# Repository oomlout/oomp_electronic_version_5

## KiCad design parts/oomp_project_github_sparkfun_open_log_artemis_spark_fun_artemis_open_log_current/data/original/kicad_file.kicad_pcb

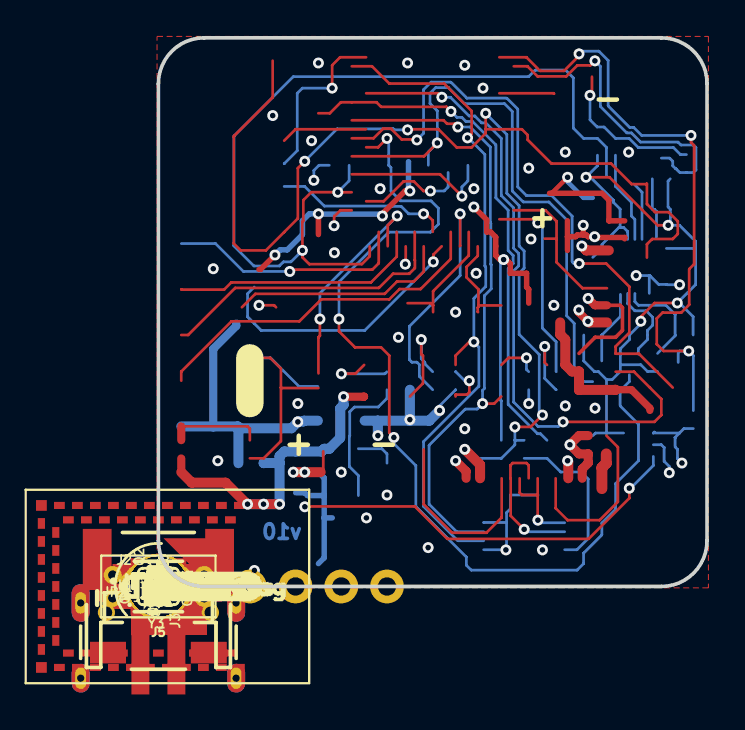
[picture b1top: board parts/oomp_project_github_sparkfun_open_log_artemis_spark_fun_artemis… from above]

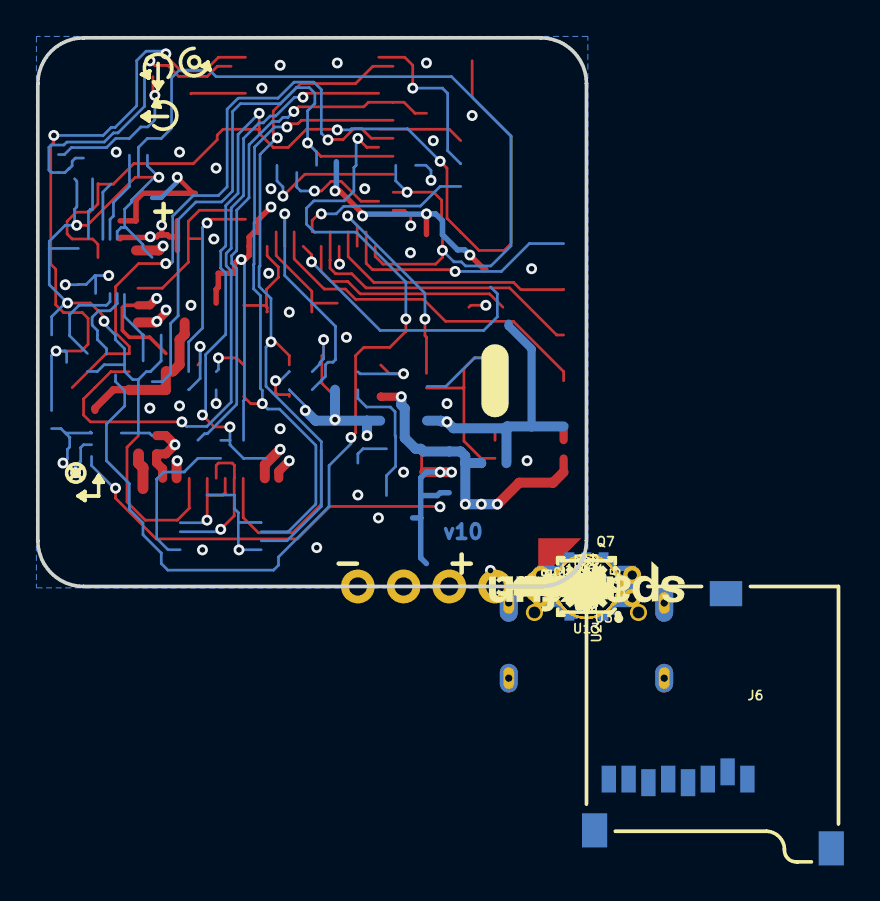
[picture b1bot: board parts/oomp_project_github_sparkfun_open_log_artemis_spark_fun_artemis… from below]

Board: 4 copper layers, 30.5 x 30.5 mm, 140 parts (74 on the bottom side), 61 nets.

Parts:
BT1: ML414H; ML414H_IV01E
C1, C33, C53, C54: 1.0uF; 0402-TIGHT
C2, C7: 2.2uF; 0402-TIGHT
C3, C4: 4.7uF; 0402-TIGHT
C5, C31, C41, C42, C43, C46, C51, C52: 0.1uF; 0402-TIGHT
C29, C30: 15pF; 0402-TIGHT
C32: 10uF; 0402-TIGHT
C40: 10nF; 0402-TIGHT
C44: 1.0nF; 0402-TIGHT
D1, D3: 3A/10V/280mV; SOD-323
D2, D11: Yellow; LED-0603
D6: 1A/23V/620mV; SOD-323
D9: BLUE; LED-0603
D12: GREEN; LED-0603
FD1, FD2, FD3, FD4: FIDUCIAL1X2; FIDUCIAL-1X2
FRAME1: FRAME-LEDGER; CREATIVE_COMMONS
GND0: TEST-POINTTP_15TH_THRU; TP_15TH
H1, H2, H3, H4: STAND-OFF
J1, J3: 1X02_NO_SILK
J2: JST-2-SMD
J4: 1X06_NO_SILK
J5: USB-C-16P_4LAYER-PADS
J6: MICRO-SD; MICRO-SD-SOCKET
J7: 1X01_NO_SILK
J11: QWIIC_RIGHT_ANGLE; JST04_1MM_RA
J14: CORTEX_JTAG; 2X5-PTH-1.27MM
JP2: MEAS; COMBO-JUMPER_2_NC_TRACE
LED1: RED; LED-0603
LOGO1: SFE_LOGO_NAME.1_INCH; SFE_LOGO_NAME_.1
LOGO2: OSHW-LOGOS; OSHW-LOGO-S
LOGO3: SPECIAL_INSTRUCTIONS-ORDERING; ORDERING_INSTRUCTIONS
LOGO4, LOGO5: SFE_LOGO_FLAME.1_INCH; SFE_LOGO_FLAME_.1
Q1, Q3, Q7, Q9, Q10: 20V/0.2A/8MHz/1.2Ω/1Vth; SOT-416FL
Q2: 20V/4.2A/52mΩ/1.4W; SOT23-3
QWIIC_3.3V0: TEST-POINTTP_15TH_THRU; TP_15TH
R1, R4, R40, R41, R44, R45, R46, R47, R48: 2.2k; 0402-TIGHT
R2: 330K; 0402-TIGHT
R3: 220k; 0402-TIGHT
R5, R22, R23, R24, R25: 1k; 0402-TIGHT
R6: 1M; 0402-TIGHT
R7: 2M; 0402-TIGHT
R8: 0; 0402-TIGHT
R26, R27: 5.1k; 0402-TIGHT
R28: 100k; 0402-TIGHT
R29: 220KOHM-0402T-1/16W-1%; 0402-TIGHT
R49: DNP; 0402-TIGHT
S3: RESET; TACTILE_SWITCH_SMD_4.6X2.8MM
SCL0: TEST-POINTTP_15TH_THRU; TP_15TH
SDA0: TEST-POINTTP_15TH_THRU; TP_15TH
TP1: TEST-POINT3; PAD.03X.03
U1: 3.0V Supervisor; SOT23-3
U2: MCP73831; SOT23-5
U3, U4: 3.3V; SOT23-5
U8: ARTEMIS_MODULE; ARTEMIS_FP
U10: CH340E; MSOP10
U13: 9DoF IMU; QFN24-3X3-ICM-20948
U14: 1.8V/100mA; SC70
U$1: QWIIC#LOGO#JPG
U$2: CHG2
U$3: PWR0
U$4: RX4
U$5: STAT5
U$6: VE0
U$7: TX3
U$8, U$12: RST0
U$9: ARTEMIS13
U$10, U$11: PSWC0
U$13: C0
U$14: D0
U$15: 30
U$27: MEAS3
U$28: OPENLOG12
U$32: RST9
U$33: VIN8
U$34, U$35: 3V34
U$36, U$37: 113
U$38, U$39: 322
U$40, U$41: GND5
U$42, U$54: RX1
U$43, U$49: X0
U$44, U$50: Y1
U$45, U$51: Z2
U$46: G5
U$47: A4
U$48: M3
U$55, U$56: TX0
VE0: SMT-JUMPER_2_NO_SILK
Y3: 32.768kHz; CRYSTAL-SMD-3.2X1.5MM

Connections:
3.3V: C2.1, C40.1, C41.1, C54.1, D6.A, J4.5, J14.1, Q2.2, R24.2, R25.2, R45.2, R47.2, R49.2, U1.3, U3.5, U10.7, U10.10, U14.1
5V: C3.1, D1.C, D2.A, J5.VBUS1, J5.VBUS2, JP2.1, JP2.3, U2.4
ARTEMIS_BOOT: C43.2, R29.2, U8.BOOT
ARTEMIS_RX0: D11.C, U8.RXI-0, U10.8
ARTEMIS_SWDCK: J14.4, U8.SWDCK
ARTEMIS_SWDIO: J14.2, U8.SWDIO
ARTEMIS_TX0: D12.C, U8.TXO-0, U10.9
ARTEMIS_~AD11: J4.1, U8.~AD11
ARTEMIS_~AD12/TX1: J4.3, U8.~AD12
ARTEMIS_~AD13/RX1: J4.2, U8.~AD13
ARTEMIS_~AD32: J4.4, U8.~AD32
ARTEMIS_~RESET: C42.2, C44.1, J7.1, J14.10, R28.1, S3.3, S3.4, U8.~RST
ARTEMIS_~RTS: C42.1, C43.1, U10.4
CC3: J5.B5, R26.2
CC4: J5.A5, R27.2
CHG_LED: R5.1, U2.1
D+2: J5.A6, J5.B6, U10.1
D-2: J5.A7, J5.B7, U10.2
DAT1: J6.DAT1, U8.~D26
DAT2: J6.DAT2, U8.~D4
GND: BT1.-, C1.2, C2.2, C3.2, C4.2, C5.2, C7.2, C29.1, C30.1, C31.1, C32.2, C33.2, C40.2, C41.2, C44.2, C46.2, C51.2, C52.2, C53.2, C54.2, D9.C, GND0.P$1, J1.2, J2.1, J3.2, J4.6, J5.GND, J5.GND2, J6.CD1, J6.GND, J6.GND1, J6.GND3, J11.1, J14.3, J14.5, J14.9, LED1.C, R3.1, R4.1, R6.1, R8.1, R26.1, R27.1, R29.1, S3.1, S3.2, U1.1, U2.2, U3.2, U4.2, U8.GND@1, U8.GND@22, U8.GND@38, U8.GND@39, U8.GND@47, U8.GND@59, U10.3, U13.18, U13.20, U14.2
ICM-20948-LV_#_1.8V: C52.1, C53.1, Q1.1, Q3.1, Q7.1, Q9.1, Q10.1, R40.2, R41.2, R44.2, R46.2, R48.2, U13.8, U13.13, U14.5
ICM-20948-LV_INT: Q7.2, R44.1, U13.12
ICM-20948-LV_SCK: Q1.2, R40.1, U13.23
ICM-20948-LV_SDI: Q3.2, R41.1, U13.24
ICM-20948-LV_SDO: Q10.2, R48.1, U13.9
ICM-20948-LV_~CS: Q9.2, R46.1, U13.22
ICM_INT: Q7.3, R45.1, U8.~D37
ICM_PWR: U8.~D27, U14.3
ICM_~CS: Q9.3, R47.1, U8.~D44
MICROSD_PWR: Q2.1, U8.D15
MICROSD_~CS: J6.CS/DAT3, U8.~D23
unnamed: J5.SHLD1, J5.SHLD2, J5.SHLD3, J5.SHLD4, R8.2
unnamed: R4.2, U2.5
unnamed: D2.C, R5.2
unnamed: C29.2, U8.XO, Y3.P$2
unnamed: C30.2, U8.XI, Y3.P$1
unnamed: LED1.A, R22.1
unnamed: D9.A, R23.1
unnamed: D12.A, R25.1
unnamed: D11.A, R24.1
unnamed: C51.1, U13.10
PWR_LED: R22.2, U8.~AD29
QWIIC_3.3V: C5.1, C7.1, J11.2, QWIIC_3.3V0.P$1, U4.5
QWIIC_PWR: R3.2, U4.3, U8.~D18
RTC_BAT+: BT1.+, D3.A, R1.1, TP1.P$1
SCK: J6.SCLK, Q1.3, U8.~D5
SCL: J11.4, SCL0.P$1, U8.D8
SDA: J11.3, SDA0.P$1, U8.D9
SDI: J6.DO/DAT0, Q10.3, R49.1, U8.~D6, U8.~D22
SDO: J6.DI/CMD, Q3.3, U8.D7
SD_PWR: C46.1, J6.VCC, Q2.3
STATLED: R23.2, U8.~D19
SWO: J14.6, U8.~AD33/SWO
VCC_1: C31.2, C32.1, C33.1, D3.C, D6.C, R1.2, R28.2, U8.VDD@36, U8.VDD@37
VIN: C1.1, JP2.2, JP2.4, R2.2, R7.2, U3.1, U4.1
VIN/3: R6.2, R7.1, U8.AD34
VREG_EN: J3.1, R2.1, U3.3, VE0.2
VREG_EN1: U8.~D25, VE0.1
V_BATT: C4.1, D1.A, J1.1, J2.2, U2.3
~POWER_LOSS: U1.2, U8.D3

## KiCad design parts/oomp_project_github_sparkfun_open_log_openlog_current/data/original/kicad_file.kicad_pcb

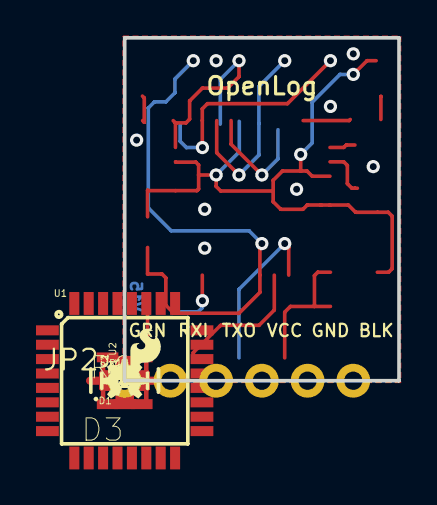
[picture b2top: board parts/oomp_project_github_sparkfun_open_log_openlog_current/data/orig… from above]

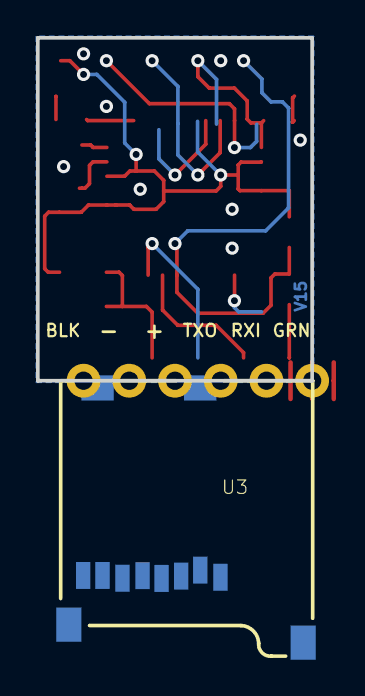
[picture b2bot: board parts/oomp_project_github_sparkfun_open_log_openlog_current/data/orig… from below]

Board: 2 copper layers, 15.2 x 19.1 mm, 26 parts (3 on the bottom side), 17 nets.

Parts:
C1: 10uF; 0603-POL
C2, C3, C4: 0.1uF; 0603-CAP
D1: BLUE; LED-0603
D3: GREEN; LED-0603
FID1, FID2, FID3, FID4: FIDUCIALUFIDUCIAL; MICRO-FIDUCIAL
FRAME1: FRAME-LETTER; CREATIVE_COMMONS
JP2: 1X06_NO_SILK
LOGO1: SFE_LOGO_FLAME.1_INCH; SFE_LOGO_FLAME_.1
LOGO2: OSHW-LOGOMINI; OSHW-LOGO-MINI
Q1: 16MHZ; RESONATOR-SMD
R1: 1K; 0603-RES
R2: 10K; 0603-RES
R6: 330; 0603-RES
TP1, TP2, TP3, TP4, TP5: TEST-POINT3; PAD.03X.03
U1: ATMEGA328P_TQFP; TQFP32-08
U2: 3.3V MIC5205; SOT23-5
U3: microSD Socket; MICROSD_1_1

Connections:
3.3V: C1.A, C3.2, C4.1, R2.2, TP1.P$1, U1.4, U1.6, U1.18, U1.20, U2.5, U3.4
CD: U1.25, U3.CD1
CS: U1.14, U3.2
DTR: C2.2, JP2.6
GND: C1.K, C3.1, C4.2, D1.C, D3.C, JP2.1, JP2.2, Q1.2, U1.3, U1.5, U1.21, U2.2, U3.6, U3.GND1, U3.GND3
MISO: TP2.P$1, U1.16, U3.7
MOSI: TP3.P$1, U1.15, U3.3
unnamed: Q1.1, U1.8
unnamed: Q1.3, U1.7
unnamed: D1.A, R1.2
unnamed: R1.1, U1.9
unnamed: D3.A, R6.2
RAW: JP2.3, U2.1, U2.3
RST: C2.1, R2.1, TP5.P$1, U1.29
RXI: JP2.5, U1.30
SCK: R6.1, TP4.P$1, U1.17, U3.5
TXO: JP2.4, U1.31

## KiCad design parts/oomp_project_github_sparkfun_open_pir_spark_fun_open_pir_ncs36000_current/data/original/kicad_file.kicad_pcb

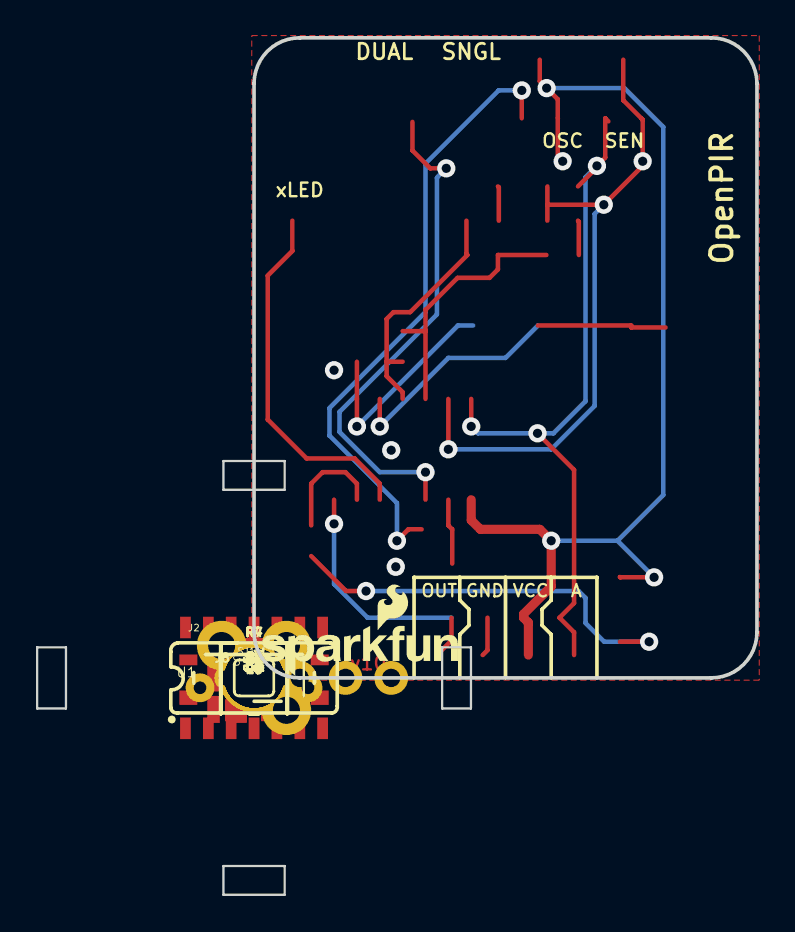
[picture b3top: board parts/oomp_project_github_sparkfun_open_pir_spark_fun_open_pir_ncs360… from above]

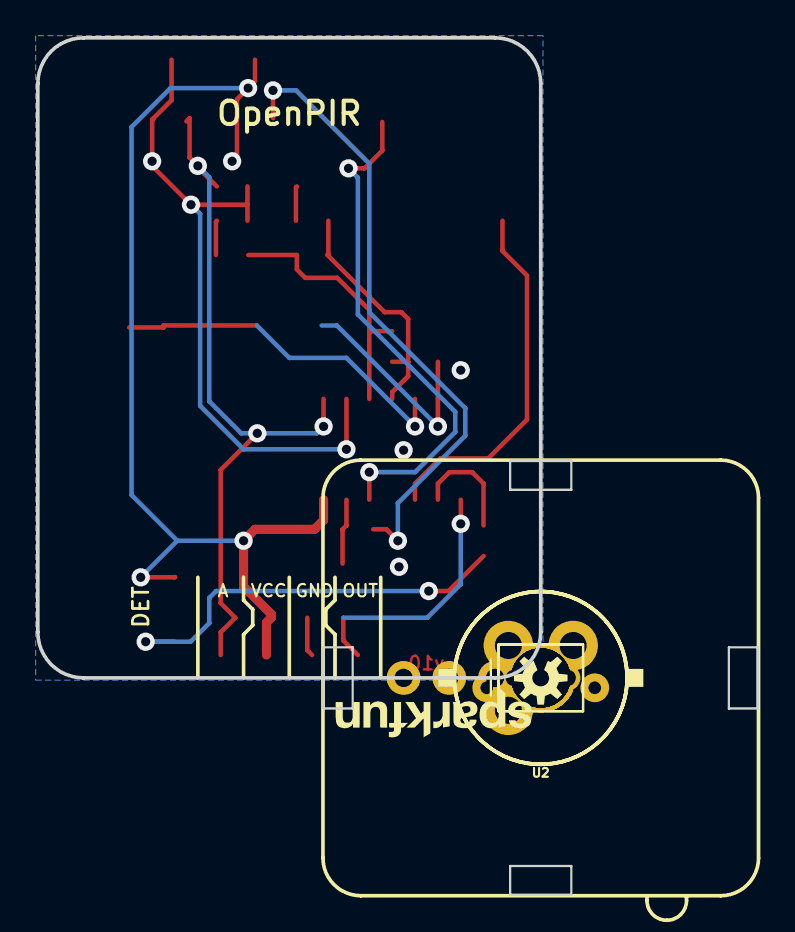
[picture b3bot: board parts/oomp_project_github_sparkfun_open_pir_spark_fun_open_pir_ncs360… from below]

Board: 2 copper layers, 27.9 x 35.6 mm, 35 parts (6 on the bottom side), 17 nets.

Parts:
C1, C3: 22uF; 0805
C2, C4: 10nF; 0603
C5, C6, C7: 0.1uF; 0603
D1: Green; LED-1206-BOTTOM
FD1, FD2: FIDUCIALUFIDUCIAL; MICRO-FIDUCIAL
FRAME1: FRAME-LETTER; CREATIVE_COMMONS
H1, H2, H3, H4: STAND-OFF
J2: JST-4-PTH-VERT-NS
J8: 1X04_NO_SILK_ALL_ROUND
LOGO1: SFE_LOGO_NAME_FLAME.1_INCH; SFE_LOGO_NAME_FLAME_.1
LOGO3: SFE_LOGO_NAME.1_INCH; SFE_LOGO_NAME_.1
LOGO4: OSHW-LOGOS; OSHW-LOGO-S
R1, R3: 10k; 0603
R2: 560k; 0603
R4, R7: 1M; TRIMPOT-TC33X
R5: 43k; 0603
R6: 51k; 0603
R8: 1k; 0603
S1: SWITCH-SPST-SMD-A
SJ1: LED-EN; SJ_2S
TP1, TP2: PAD.03X.05
U1: NCS36000; SO14
U2: PIR
U$1: CWM 0.5 GI V1; LENS-CWM-0.5-GI-V1

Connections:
A_OUT: C4.2, J2.1, J8.1, R4.1, U1.1
GND: C5.2, C6.2, C7.2, J2.3, J8.3, R1.1, R5.1, S1.3, SJ1.2, U1.7, U2.G
LED: R8.1, U1.9
MODE: S1.2, U1.12
unnamed: C5.1, R5.2, U1.5, U2.S
unnamed: C6.1, U1.6, U2.D
unnamed: C1.2, R1.2
unnamed: C3.2, R3.2
unnamed: C1.1, C2.2, R2.1, U1.4
unnamed: C2.1, C3.1, R2.2, U1.3
unnamed: C4.1, R3.1, R4.2, R4.3, TP1.P$1, U1.2
unnamed: C7.1, R6.1, U1.13
unnamed: D1.C, R8.2
unnamed: R6.2, R7.1
OUT: J2.4, J8.4, U1.8
VCC: D1.A, J2.2, J8.2, R7.2, R7.3, TP2.P$1, U1.14
~LED_EN: SJ1.1, U1.10

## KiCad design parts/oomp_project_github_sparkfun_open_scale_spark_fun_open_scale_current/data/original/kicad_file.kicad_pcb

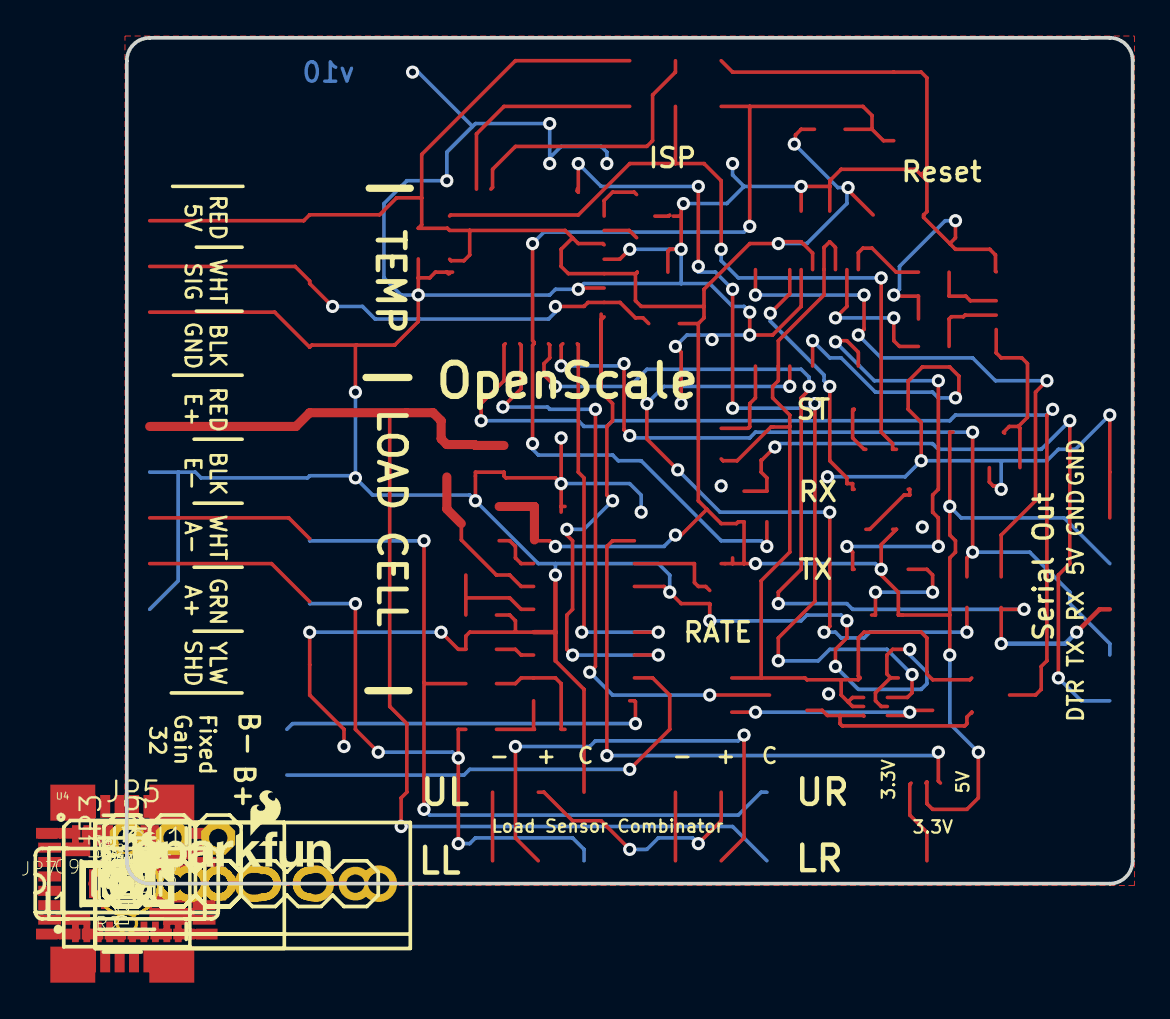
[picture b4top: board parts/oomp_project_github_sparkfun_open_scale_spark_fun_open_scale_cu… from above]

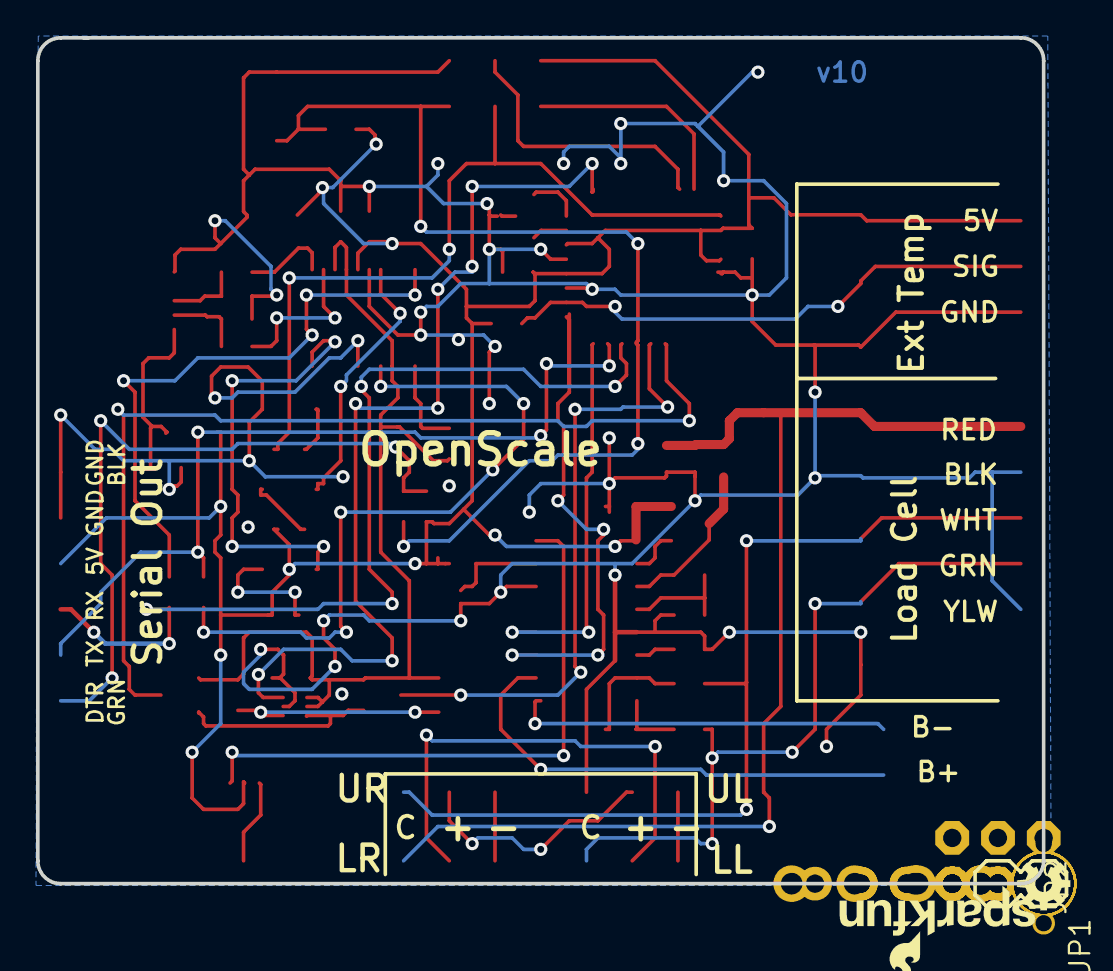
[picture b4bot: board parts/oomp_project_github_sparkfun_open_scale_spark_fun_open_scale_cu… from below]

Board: 2 copper layers, 55.9 x 47.0 mm, 75 parts (4 on the bottom side), 51 nets.

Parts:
C1, C3, C6, C7, C8, C10, C11, C14, C16: 0.1uF; 0603-CAP
C2, C5: 47pF; 0603-CAP
C4, C12, C13: 1.0uF; 0603-CAP
C9: 10uF; EIA3216
D1: Yellow; LED-1206
D2: GREEN; LED-1206
D3: BLUE; LED-1206
F1: PTCSMD; PTC-1206
FID1, FID2: FIDUCIALUFIDUCIAL; MICRO-FIDUCIAL
FRAME1: FRAME-LEDGER; CREATIVE_COMMONS
J1: 3.3V; 1X01
J2: UL; 1X03
J3: UR; 1X03
J4: LL; 1X03
J5: LR; 1X03
JP1: Temp; 1X03_NO_SILK
JP2: Fixed Gain 32; 1X02
JP3: Load; 1X05_NO_SILK
JP4: Screw; SCREWTERMINAL-3.5MM-3_LOCK.007S
JP5: AVR_PRG; 2X3
JP6: JUMPER-PAD-3-2OF3_NC_BY_PASTE; PAD-JUMPER-3-2OF3_NC_BY_PASTE_YES_SILK_FULL_BOX
JP7: USBSMD; USB-MINIB
JP9: FTDI_BASIC
JP11: Screw Terminals; SCREWTERMINAL-3.5MM-5
L1: 3.3uH; 0805
LOGO1, LOGO4: SFE_LOGO_NAME_FLAME.1_INCH; SFE_LOGO_NAME_FLAME_.1
LOGO2, LOGO5: OSHW-LOGOS; OSHW-LOGO-S
LOGO3: SFE_LOGO_FLAME.1_INCH; SFE_LOGO_FLAME_.1
Q1, Q2: 200mA/50V; SOT23-3
Q3: MMBT4403; SOT23-3
Q4: MOSFET-NCHANNEL2N7002PW; SOT323
R1, R6: 27; 0603
R2, R7, R10, R18: 10K; 0603-RES
R3, R4: 100; 0603-RES
R5, R11, R12, R13, R15: 1K; 0603-RES
R8, R9, R14: 4.7K; 0603-RES
R16: 20k; 0603-RES
R17: 8.2K; 0603-RES
S2: Reset; TACTILE-SWITCH-SMD
SJ2: JUMPER-PAD-2-NC_BY_PASTE; PAD-JUMPER-2-NC_BY_PASTE_YES_SILK
STANDOFF1, STANDOFF2, STANDOFF3, STANDOFF4: STAND-OFF
U1: HX711; SO16
U3: TMP102; SOT563
U4: ATMEGA328P_TQFP; TQFP32-08
U6: FT231XS; SSOP20_L
Y2: 16MHZ; RESONATOR-SMD

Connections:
2: J4.2, J5.2
3.3V: C3.1, C10.1, Q1.1, Q2.1, Q4.1, R8.2, R9.2, R10.2, U3.4, U3.5, U6.3, U6.13, U6.14
5V: C4.1, C6.1, C7.1, C9.A, C13.1, F1.2, JP1.1, JP4.1, JP5.2, JP6.2, JP9.VCC, Q3.2, R2.2, R7.2, R13.2, R14.2, R15.2, R18.2, U1.1, U4.4, U4.6, U4.18, U4.20, U6.15
A+: J4.3, JP3.2, JP11.4, R4.1
A-: J3.3, JP3.3, JP11.3, R3.1
ALERT: U3.3, U4.9
AVDD: C12.2, C16.1, J5.3, JP3.5, JP11.1, L1.1
B+: JP2.1, U1.10
B-: JP2.2, U1.9
D11: JP5.4, U4.15
D12: JP5.1, U4.16
D13: JP5.3, R5.2, U4.17
DTR: C1.1, JP9.DTR, Q4.3, R18.1
GND: C2.2, C3.2, C4.2, C5.2, C6.2, C7.2, C9.C, C10.2, C11.1, C12.1, C13.2, C14.2, C16.2, D3.C, J2.3, JP1.3, JP3.1, JP3.4, JP4.3, JP5.6, JP7.GND, JP9.CTS, JP9.GND, JP11.2, JP11.5, R17.1, S2.1, SJ2.1, U1.5, U1.14, U3.2, U4.3, U4.5, U4.21, U6.6, U6.16, Y2.2
LC_DOUT: U1.12, U4.32
LC_SCK: U1.11, U4.1
LV_SCL: Q2.2, R8.1, U3.1
LV_SDA: Q1.2, R9.1, U3.6
unnamed: U4.7, Y2.1
unnamed: D3.A, R5.1
unnamed: U4.8, Y2.3
unnamed: C5.1, JP7.D-, R6.1
unnamed: D1.A, R13.1
unnamed: D2.A, R15.1
unnamed: C2.1, JP7.D+, R1.1
unnamed: R6.2, U6.12
unnamed: R7.1, SJ2.2, U1.15
unnamed: C8.1, R3.2, U1.7
unnamed: C8.2, R4.2, U1.8
unnamed: C14.1, F1.1, JP7.VBUS
unnamed: R1.2, U6.11
unnamed: R12.2, U6.4
unnamed: JP6.3, U1.16
unnamed: R11.2, U6.20
unnamed: Q3.1, U1.2
unnamed: R16.1, R17.2, U1.4
unnamed: J1.1, JP6.1
unnamed: J2.2, J3.2
unnamed: C11.2, U1.6
unnamed: J2.1, J4.1
unnamed: J3.1, J5.1
unnamed: Q4.2, R10.1, U6.1
RIPUP@: L1.2, Q3.3, R16.2, U1.3
RST: C1.2, JP5.5, R2.1, S2.3, U4.29
RXD: JP9.TXO, R11.1, U4.30
RXLED: D1.C, U6.17
SCL: Q2.3, U4.28
SDA: Q1.3, U4.27
TEMP_DAT: JP1.2, JP4.2, R14.1, U4.2
TXD: JP9.RXI, R12.1, U4.31
TXLED: D2.C, U6.10

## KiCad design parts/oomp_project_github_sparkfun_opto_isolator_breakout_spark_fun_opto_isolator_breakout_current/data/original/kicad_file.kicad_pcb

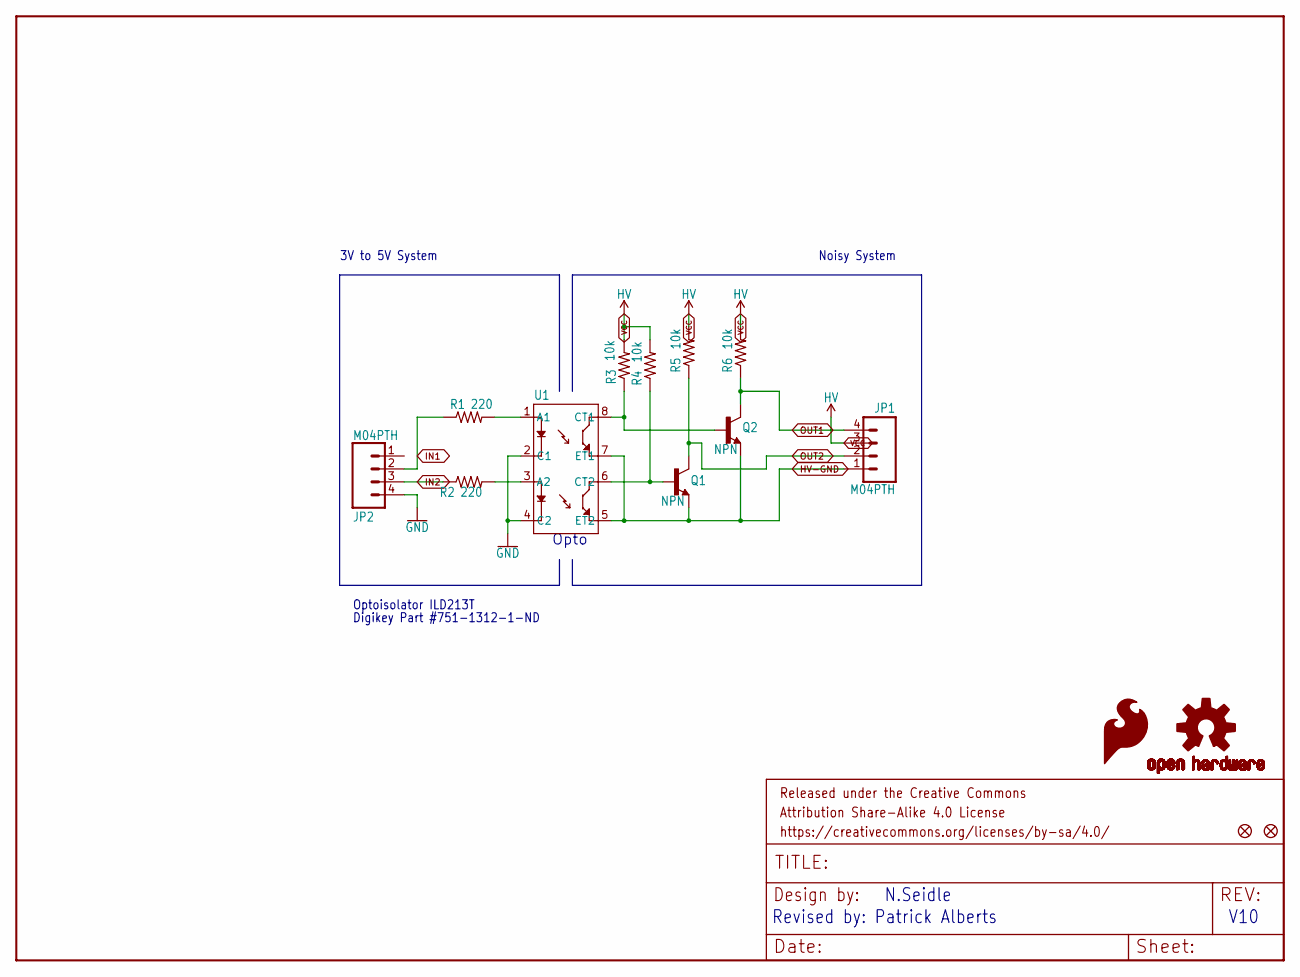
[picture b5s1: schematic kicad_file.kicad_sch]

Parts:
FRAME1: FRAME-LETTER; CREATIVE_COMMONS
JP1, JP2: M04PTH; 1X04
LOGO1: OSHW-LOGOS; OSHW-LOGO-S
LOGO2: SFE_LOGO_FLAME.1_INCH; SFE_LOGO_FLAME_.1
Q1, Q2: NPN; SOT23-3
R1, R2: 220; 0603
R3, R4, R5, R6: 10k; 0603
U1: ILD213T-IDL213T; SO08
U$2, U$3: FIDUCIALUFIDUCIAL; MICRO-FIDUCIAL

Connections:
GND: JP2.4, U1.2 (C1), U1.4 (C2)
HV-GND: JP1.1, Q1.2 (E), Q2.2 (E), U1.5 (ET2), U1.7 (ET1)
IN1: JP2.2, R1.1
IN2: JP2.3, R2.1
unnamed: R1.2, U1.1 (A1)
unnamed: R2.2, U1.3 (A2)
OUT1: JP1.4, Q2.3 (C), R6.1
OUT1N: Q2.1 (B), R3.1, U1.8 (CT1)
OUT2: JP1.2, Q1.3 (C), R5.1
OUT2N: Q1.1 (B), R4.1, U1.6 (CT2)
VCC: JP1.3, R3.2, R4.2, R5.2, R6.2

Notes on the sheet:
Optoisolator ILD213T
Opto
Noisy System
V10
Digikey Part #751-1312-1-ND
N.Seidle
3V to 5V System
Revised by: Patrick Alberts

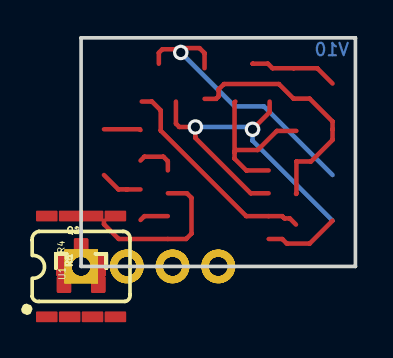
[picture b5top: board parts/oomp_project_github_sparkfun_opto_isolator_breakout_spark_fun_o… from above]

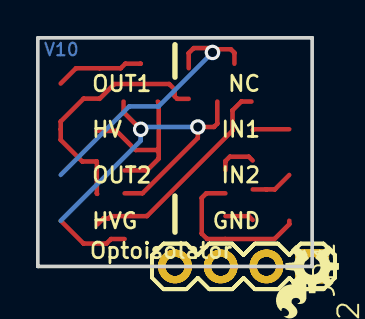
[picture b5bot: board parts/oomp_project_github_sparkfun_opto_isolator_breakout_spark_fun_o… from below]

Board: 2 copper layers, 15.2 x 12.7 mm, 16 parts (4 on the bottom side), 11 nets.

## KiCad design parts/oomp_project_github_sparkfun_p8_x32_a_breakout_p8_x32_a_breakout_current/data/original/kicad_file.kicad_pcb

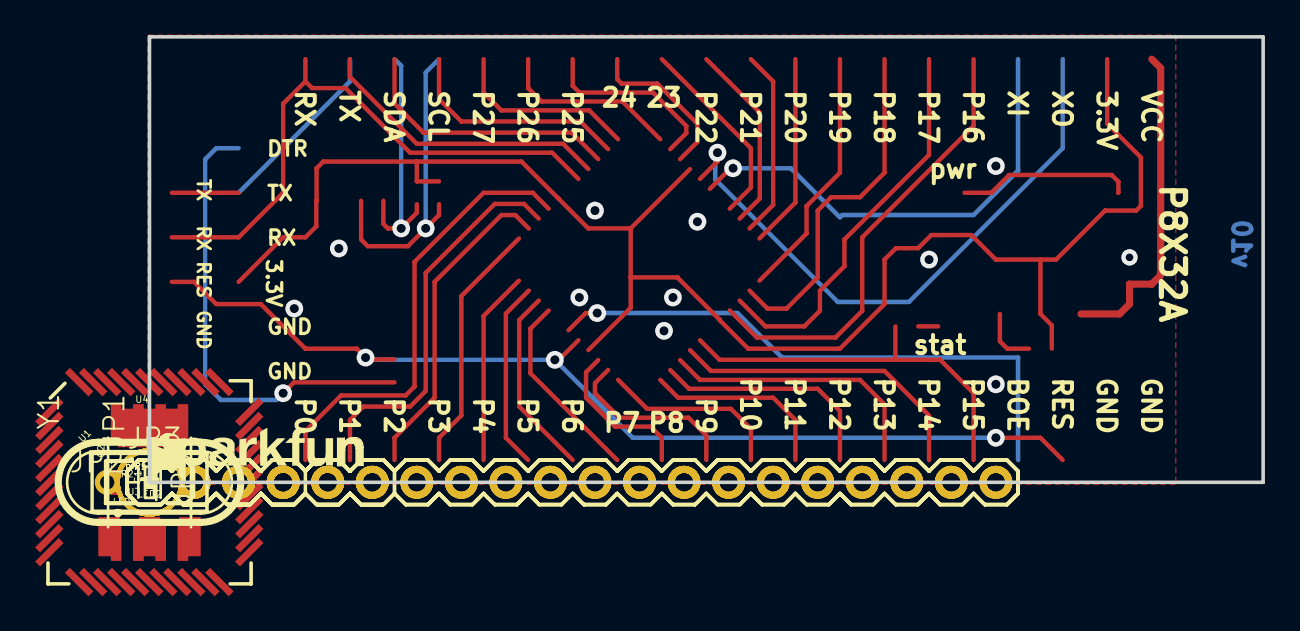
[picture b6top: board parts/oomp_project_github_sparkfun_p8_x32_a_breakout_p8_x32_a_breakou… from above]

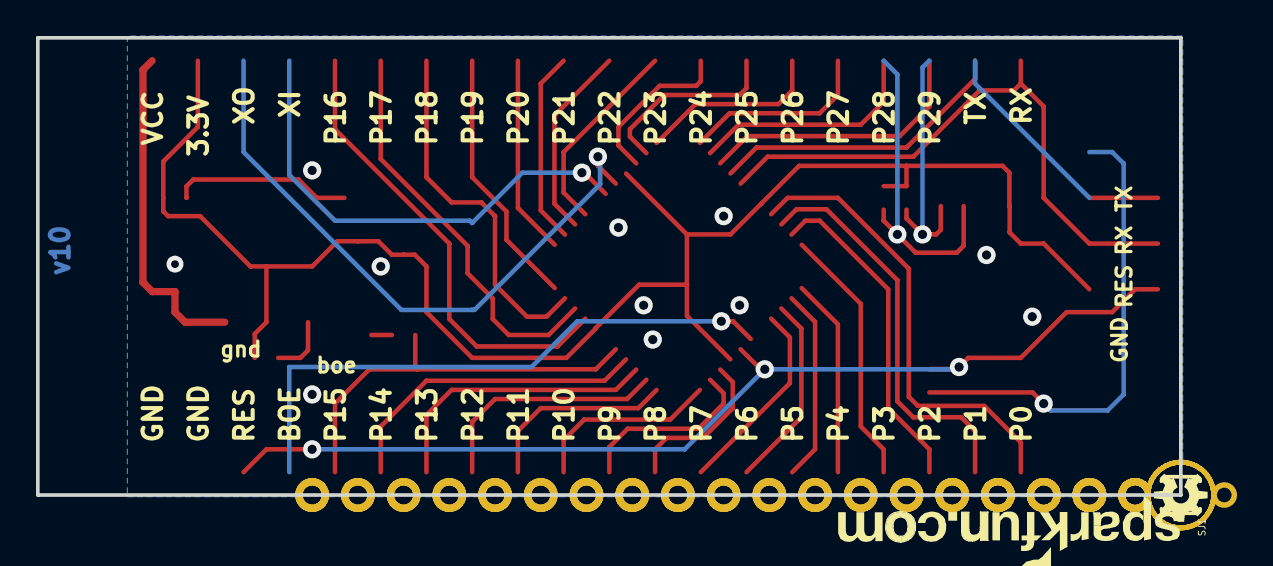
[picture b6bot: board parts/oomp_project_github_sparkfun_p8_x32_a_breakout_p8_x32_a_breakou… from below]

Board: 2 copper layers, 63.5 x 25.4 mm, 34 parts (3 on the bottom side), 43 nets.

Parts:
C1, C4: 0.1uF; 0402-CAP
C2, C3: 10uF; EIA3216
FRAME1: FRAME-LETTER; CREATIVE_COMMONS
JP1: PropPlug; 1X04
JP2, JP3: M20; 1X20
JP4, JP15: FIDUCIALUFIDUCIAL; MICRO-FIDUCIAL
JP5: LOGO-SFENEW; SFE-NEW-WEBLOGO
JP6, JP7, JP8: LOGO-SFESK; SFE-LOGO-FLAME
JP9: FTDI_BASICPTH; FTDI_BASIC
JP10, JP11, JP12, JP13: STAND-OFF
JP14: LOGO-SFENW2; SFE-NEW-WEB
LED1: red; LED-0603
LED2: yellow; LED-0603
R1, R2: 330; 0402-RES
R3, R6: 10k; 0402-RES
R4: 240; 0402-RES
R5: 390; 0402-RES
SJ1: SOLDERJUMPERTRACE; SJ_2S-TRACE
U1: P8X32A-Q44
U3: EEPROM-I2CEIAJ; SO08-EIAJ
U4: V_REG_317SMD; SOT223
U$1: OSHW-LOGOS; OSHW-LOGO-S
Y1: HC49U-V

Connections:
3.3V: C1.1, C2.A, JP3.19, JP9.VCC, R1.2, R3.2, R4.2, R6.2, U1.8, U1.18, U1.30, U1.40, U3.8, U4.2
BOE: JP2.4, SJ1.2, U1.6
GND: C1.2, C2.C, C3.C, JP1.1, JP2.1, JP2.2, JP9.CTS, JP9.GND, LED1.C, LED2.C, R5.1, SJ1.1, U1.5, U1.17, U1.27, U1.39, U3.1, U3.2, U3.3, U3.4, U3.7
unnamed: LED1.A, R1.1
unnamed: LED2.A, R2.1
unnamed: R4.1, R5.2, U4.1
unnamed: C4.1, JP9.DTR
P0: JP2.20, U1.41
P1: JP2.19, U1.42
P2: JP2.18, U1.43
P3: JP2.17, U1.44
P4: JP2.16, U1.1
P5: JP2.15, U1.2
P6: JP2.14, U1.3
P7: JP2.13, U1.4
P8: JP2.12, U1.9
P9: JP2.11, U1.10
P10: JP2.10, U1.11
P11: JP2.9, U1.12
P12: JP2.8, U1.13
P13: JP2.7, U1.14
P14: JP2.6, U1.15
P15: JP2.5, R2.2, U1.16
P16: JP3.16, U1.19
P17: JP3.15, U1.20
P18: JP3.14, U1.21
P19: JP3.13, U1.22
P20: JP3.12, U1.23
P21: JP3.11, U1.24
P22: JP3.10, U1.25
P23: JP3.9, U1.26
P24: JP3.8, U1.31
P25: JP3.7, U1.32
P26: JP3.6, U1.33
P27: JP3.5, U1.34
RES: C4.2, JP1.2, JP2.3, U1.7
RX: JP1.3, JP3.1, JP9.TXO, U1.38
SCL: JP3.4, R6.1, U1.35, U3.6
SDA: JP3.3, R3.1, U1.36, U3.5
TX: JP1.4, JP3.2, JP9.RXI, U1.37
VCC: C3.A, JP3.20, U4.3
XI: JP3.17, U1.28, Y1.2
XO: JP3.18, U1.29, Y1.1

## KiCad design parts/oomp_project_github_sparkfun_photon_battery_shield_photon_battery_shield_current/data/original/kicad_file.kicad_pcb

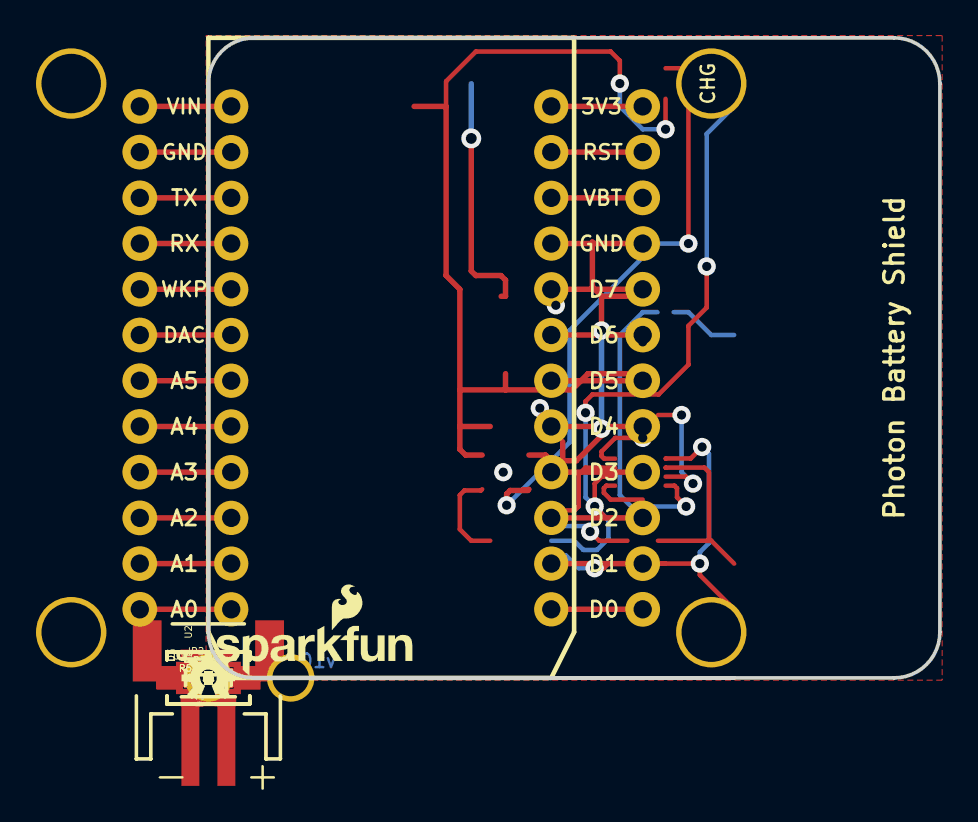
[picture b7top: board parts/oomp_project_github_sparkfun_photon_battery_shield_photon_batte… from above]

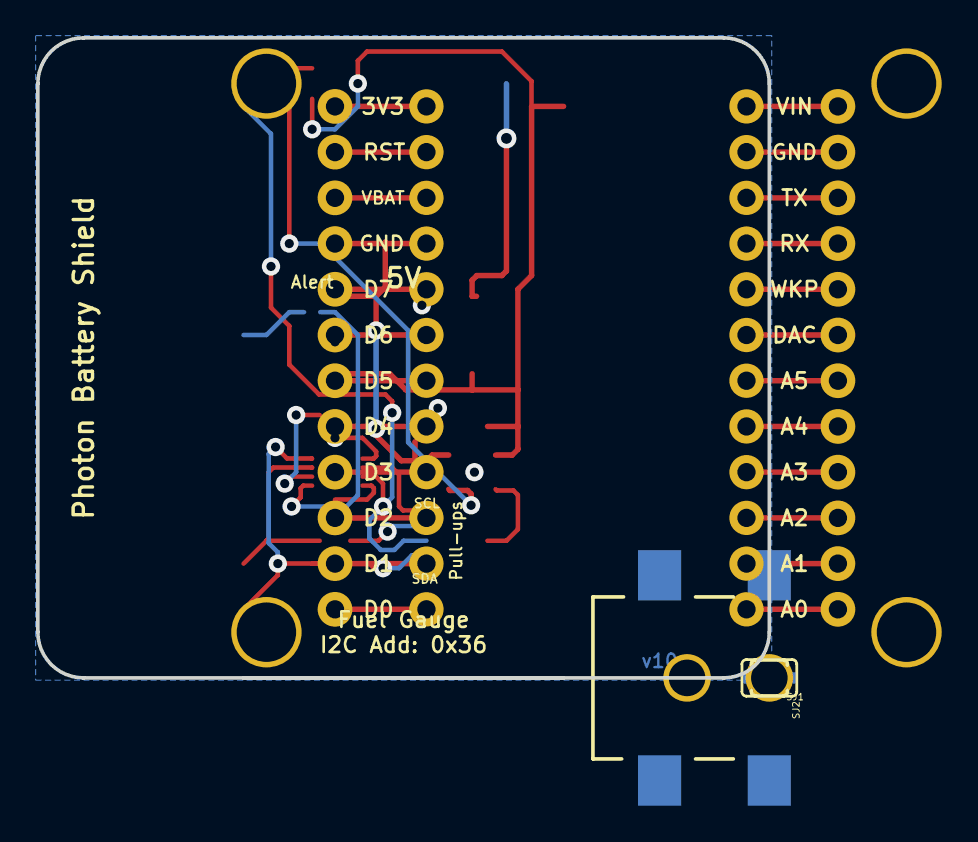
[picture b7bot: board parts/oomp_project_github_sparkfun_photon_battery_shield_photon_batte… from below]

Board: 2 copper layers, 40.6 x 35.6 mm, 25 parts (4 on the bottom side), 16 nets.

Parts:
C1, C3: 4.7uF; 0603-CAP
C2: 1.0uF; 0603-CAP
D1, D3: MBRA140; SMA-DIODE
D2: RED; LED-0603
FID1, FID2: FIDUCIAL1X2; FIDUCIAL-1X2
FRAME1: CREATIVE_COMMONS
JP1: 5.5x2.1mm Barrel; POWER_JACK_SMD
JP2: JST-2-SMD
JP3: SPARK_PHOTONTEMPLATE_WIDE; SPARK_PHOTON_TEMPLATE_WIDE
LOGO2: OSHW-LOGOS; OSHW-LOGO-S
LOGO3: SFE_LOGO_NAME_FLAME.1_INCH; SFE_LOGO_NAME_FLAME_.1
R1, R4: 1K; 0603-RES
R2: 330; 0603-RES
R3: 2.0k; 0603-RES
R5, R6: 10K; 0603-RES
SJ1: alert; PAD-JUMPER-2-NO_YES_SILK
SJ2: PAD-JUMPER-3-3OF3_NC_BY_TRACE_YES_SILK_FULL_BOX
TP1: TEST-POINT3X5; PAD.03X.05
U1: MAX1704X; TDFN-8
U2: MCP73831; SOT23-5

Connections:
3.3V: C2.1, JP3.3V3, JP3.24, SJ2.2, U1.3
D6: JP3.19, JP3.D6, SJ1.1
GND: C1.2, C2.2, C3.2, JP1.GND, JP1.P$4, JP2.1, JP3.2, JP3.21, JP3.GND@0, JP3.GND@2, R1.1, R3.2, U1.1, U1.4, U1.EP, U2.2
unnamed: D2.A, R2.2
unnamed: D2.C, U2.1
unnamed: R3.1, U2.5
unnamed: SJ1.2, U1.5
unnamed: R4.1, U1.2
unnamed: R1.2, U1.6
unnamed: R5.2, SJ2.3
unnamed: D1.A, JP1.VIN0
unnamed: R6.2, SJ2.1
SCL: JP3.14, JP3.D1, R6.1, U1.7
SDA: JP3.13, JP3.D0, R5.1, U1.8
VBAT: C3.1, D3.A, JP2.2, R4.2, TP1.P$1, U2.3
VIN: C1.1, D1.C, D3.C, JP3.1, JP3.VIN, R2.1, U2.4

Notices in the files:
parts/oomp_project_github_sparkfun_opto_isolator_breakout_spark_fun_opto_isolator_breakout_current/data/original/kicad_file.kicad_sch:
Released under the Creative Commons
https://creativecommons.org/licenses/by-sa/4.0
parts and their libraries:
Released under the Creative Commons Attribution Share-Alike 4.0 License
Released under the Creative Commons Attribution Share-Alike 3.0 License
http://creativecommons.org/licenses/by-sa/3.0
